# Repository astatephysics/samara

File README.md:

# samara
Red Wolf Space Program's samara-style glider payload

----------------------------------------------------------
## Overview

Samara are a fruit with a fibrous wing-like structure that increases their wind-borne dispersal distances. Some of these like maple and ash seeds may slow their descent by autorotation as such they provide much entertainment for us humans who find them about. This project seeks to develop an airborne payload that mimic this behavior with a 3d printed airframe housing a radio antenna and this printed circuit board. 

This version of the board is contstrained to a 30.5mm x 30.5mm board and is inspired by "CricketSATs." This consists of a RP2040 microcontroller, BME280 temperature/humidity/pressure sensor, BNO055 inertial measurement unit, and RF95 LoRA radio. Several indicator leds are included as well as a surface mounted piezo buzzer. A STEMMA/Qwiic-compatable JST connector provides access to peripheral boards over I2C (e.g., GPS breakout board, realtime clocks, science payloads.)

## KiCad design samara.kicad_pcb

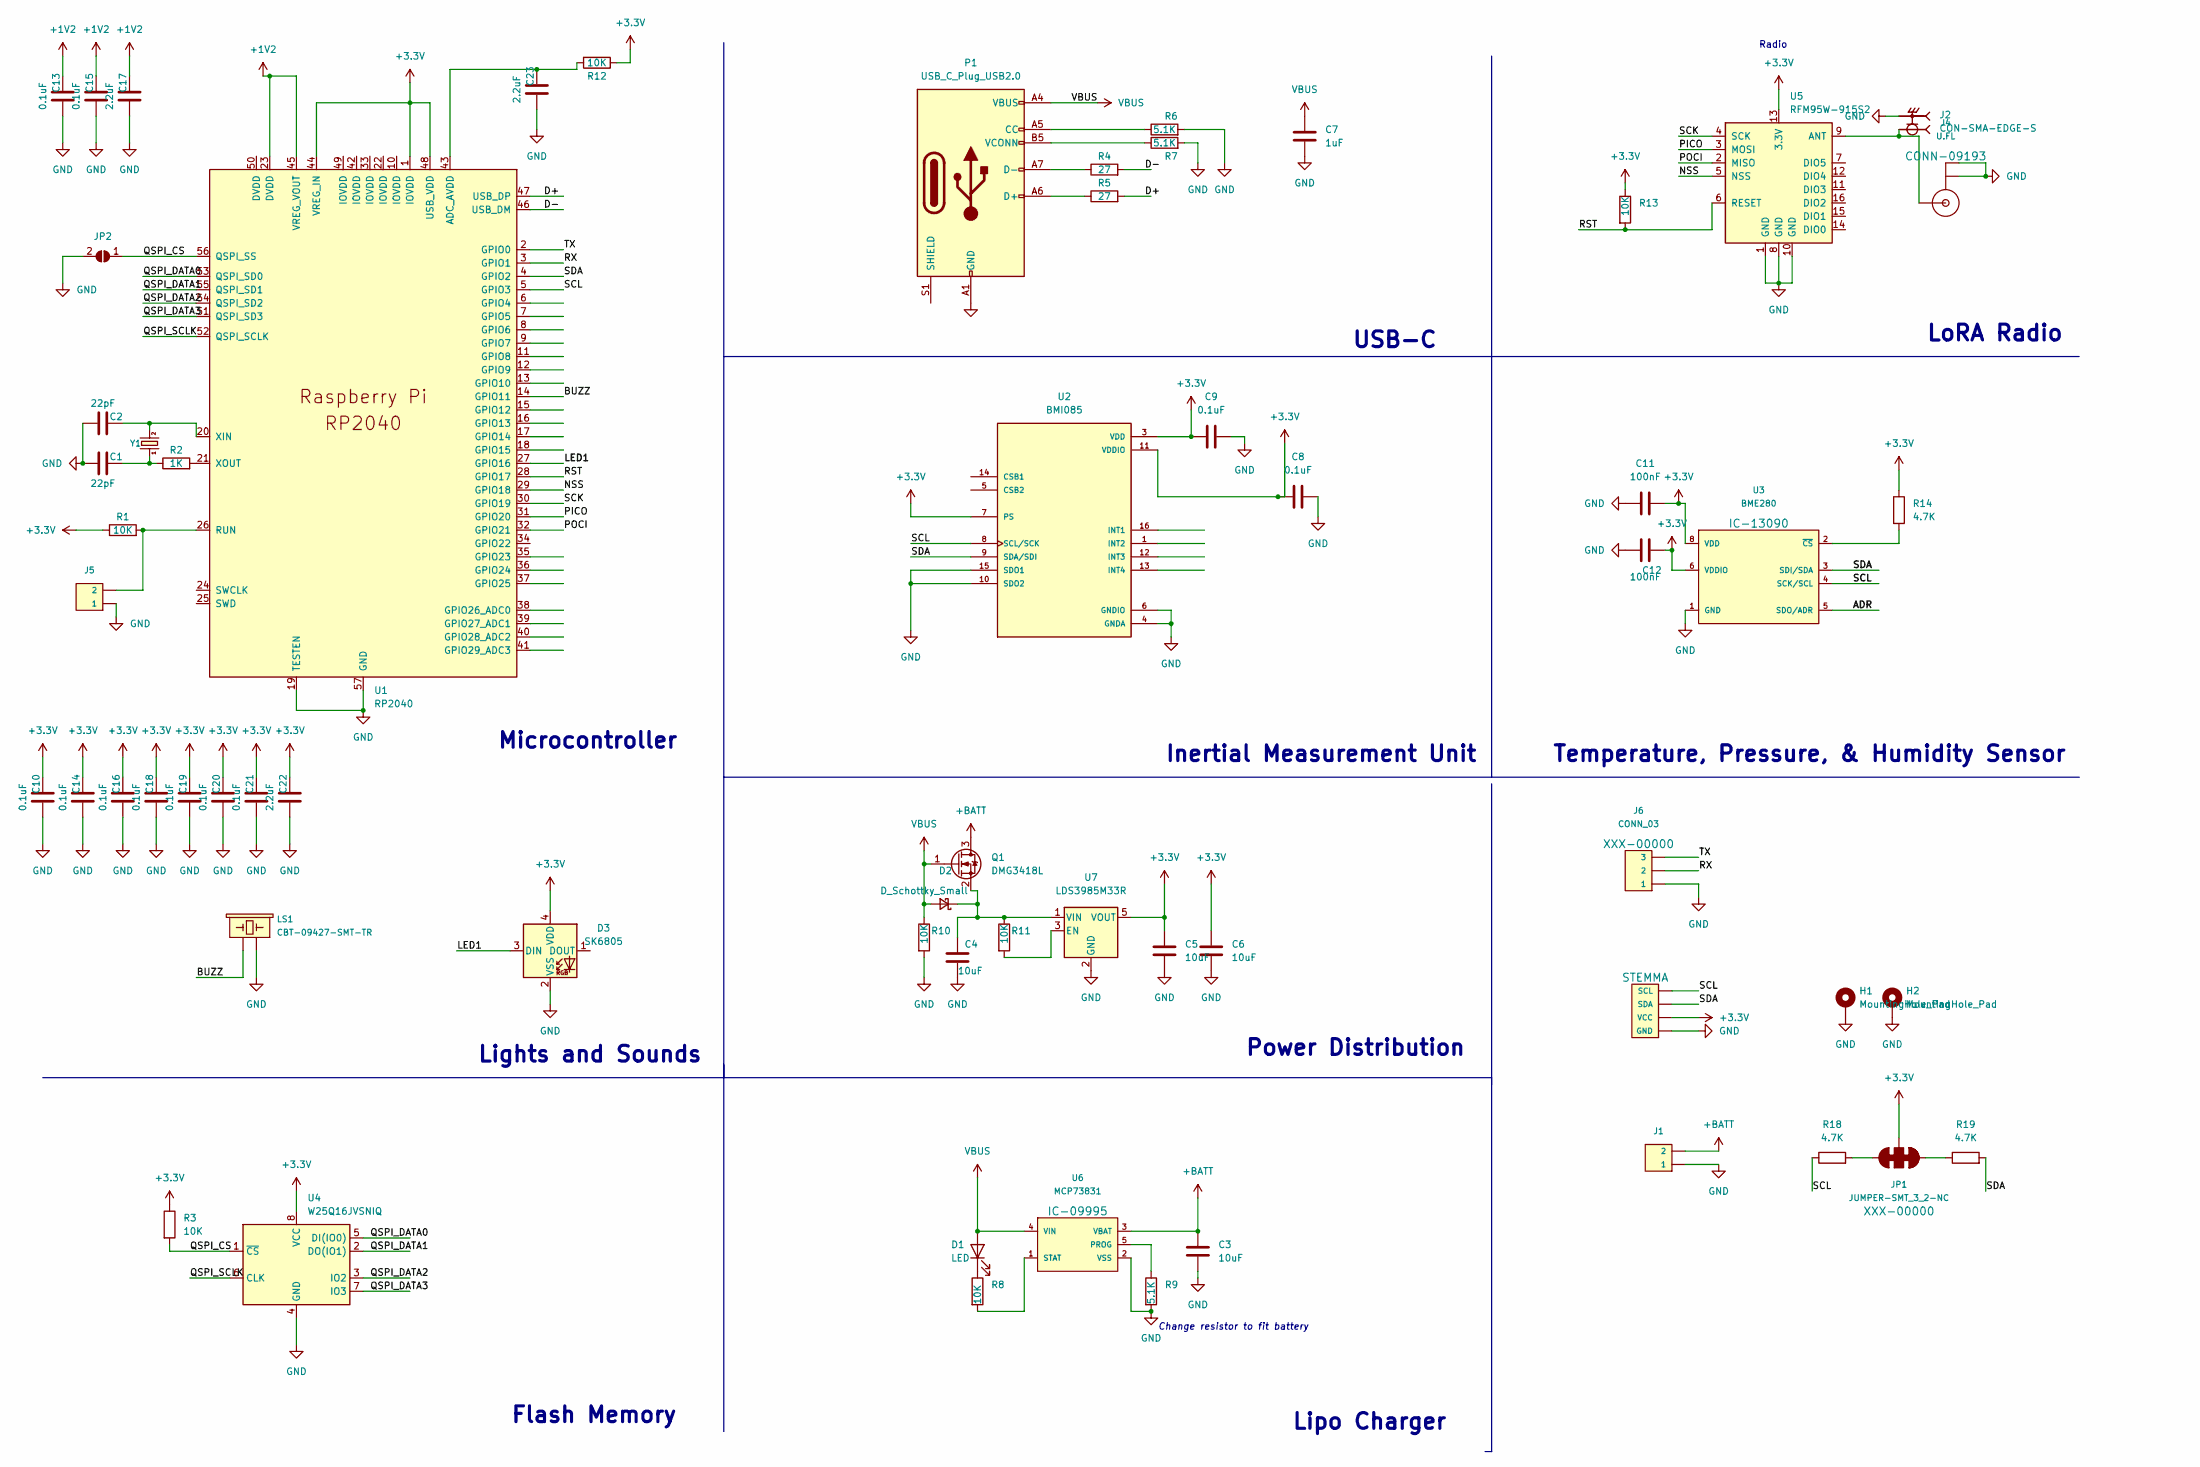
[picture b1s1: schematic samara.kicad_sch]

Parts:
C1, C2: 22pF; C_0402_1005Metric
C3, C4, C5, C6: 10uF; C_0402_1005Metric
C7: 1uF; C_0402_1005Metric
C8, C9, C10, C13, C14, C15, C16, C18, C19, C20, C21: 0.1uF; C_0402_1005Metric
C11, C12: 100nF; C_0402_1005Metric
C17, C22, C23: 2.2uF; C_0402_1005Metric
D1: LED; LED_0603_1608Metric
D2: D_Schottky_Small; D_SOD-128
D3: SK6805; LED_SK6805_PLCC4_2.4x2.7mm_P1.3mm
H1, H2: MountingHole_Pad; MountingHole_2.2mm_M2_DIN965_Pad_TopBottom
J1: CONN_02JST-PTH-2; JST_PH_S2B-PH-SM4-TB_1x02-1MP_P2.00mm_Horizontal
J2: CON-SMA-EDGE-S; RFSOLUTIONS_CON-SMA-EDGE-S; PARTREV 1
J3: I2C_STANDARDQWIIC; 1X04_1MM_RA
J4: U.FL
J5: CONN_02; 1X02
J6: CONN_03; 1X03
JP1: JUMPER-SMT_3_2-NC; SMT-JUMPER_3_2-NC_TRACE_SILK
JP2: SolderJumper_2_Open; SMT-JUMPER_2_NO_NO-SILK
LS1: CBT-09427-SMT-TR; BUZZER-CCV-KIT
P1: USB_C_Plug_USB2.0; USB_C_Receptacle_XKB_U262-16XN-4BVC11
Q1: DMG3418L; SOT-23
R1, R3, R8, R10, R11, R12, R13: 10K; R_0402_1005Metric
R2: 1K; R_0402_1005Metric
R4, R5: 27; R_0402_1005Metric
R6, R7, R9: 5.1K; R_0402_1005Metric
R14, R18, R19: 4.7K; R_0402_1005Metric
U1: RP2040; RP2040-QFN-56
U2: BMI085; PQFN50P450X300X100-16N; PARTREV 1.4
U3: BME280; LGA-8-2.5X2.5
U4: W25Q16JVSNIQ; SOIC-8_3.9x4.9mm_P1.27mm
U5: RFM95W-915S2; HOPERF_RFM9XW_SMD
U6: MCP73831; SOT-23-5
U7: LDS3985M33R; SOT-23-5
Y1: CRYSTAL-12MHZ"; CRYSTAL-SMD-3.2X2.5MM

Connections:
+1V2: C13.2, C15.2, C17.2, U1.23 (DVDD), U1.45 (VREG_VOUT)
+3V3: C5.1, C6.1, C8.1, C9.1, C10.2, C11.2, C12.2, C14.2, C16.2, C18.2, C19.2, C20.2, C21.2, C22.2, D3.4 (VDD), J3.2 (VCC), JP1.2, R1.1, R3.1, R12.1, R13.1, R14.1, U1.1 (IOVDD), U1.44 (VREG_IN), U1.48 (USB_VDD), U2.3 (VDD), U2.7 (PS), U2.11 (VDDIO), U3.6 (VDDIO), U3.8 (VDD), U4.8 (VCC), U5.13 (3.3V), U7.5 (VOUT)
+BATT: C3.1, J1.2, Q1.3 (D), U6.3 (VBAT)
/ADR: U3.5 (SDO/ADR)
/BUZZ: LS1.+ (1), U1.14 (GPIO11)
/D+: R5.2, U1.47 (USB_DP)
/D-: R4.2, U1.46 (USB_DM)
/LED1: D3.3 (DIN), U1.27 (GPIO16)
/NSS: U1.29 (GPIO18), U5.5 (NSS)
/PICO: U1.31 (GPIO20), U5.3 (MOSI)
/POCI: U1.32 (GPIO21), U5.2 (MISO)
/QSPI_CS: JP2.1 (A), R3.2, U1.56 (QSPI_SS), U4.1 (~CS)
/QSPI_DATA0: U1.53 (QSPI_SD0), U4.5 (DI(IO0))
/QSPI_DATA1: U1.55 (QSPI_SD1), U4.2 (DO(IO1))
/QSPI_DATA2: U1.54 (QSPI_SD2), U4.3 (IO2)
/QSPI_DATA3: U1.51 (QSPI_SD3), U4.7 (IO3)
/QSPI_SCLK: U1.52 (QSPI_SCLK), U4.6 (CLK)
/RST: R13.2, U1.28 (GPIO17), U5.6 (RESET)
/RX: J6.2, U1.3 (GPIO1)
/SCK: U1.30 (GPIO19), U5.4 (SCK)
/SCL: J3.4 (SCL), R18.1, U1.5 (GPIO3), U2.8 (SCL/SCK), U3.4 (SCK/SCL)
/SDA: J3.3 (SDA), R19.2, U1.4 (GPIO2), U2.9 (SDA/SDI), U3.3 (SDI/SDA)
/TX: J6.3, U1.2 (GPIO0)
GND: C1.1, C2.1, C3.2, C4.2, C5.2, C6.2, C7.2, C8.2, C9.2, C10.1, C11.1, C12.1, C13.1, C14.1, C15.1, C16.1, C17.1, C18.1, C19.1, C20.1, C21.1, C22.1, C23.1, D3.2 (VSS), H1.1, H2.1, J1.1, J2.G1, J2.G2, J2.G3, J2.G4, J3.1 (GND), J4.1 (GND), J4.2 (GND), J5.1, J6.1, JP2.2 (B), LS1.- (2), P1.A1 (GND), P1.A12 (GND), P1.B1 (GND), P1.B12 (GND), R6.2, R7.2, R9.2, R10.2, U1.19 (TESTEN), U1.57 (GND), U2.4 (GNDA), U2.6 (GNDIO), U2.10 (SDO2), U2.15 (SDO1), U3.1 (GND), U3.7 (GND), U4.4 (GND), U5.1 (GND), U5.8 (GND), U5.10 (GND), U6.2 (VSS), U7.2 (GND)
unnamed: C1.2, R2.1, Y1.1
unnamed: C2.2, U1.20 (XIN), Y1.3 (2)
unnamed: C4.1, D2.1 (K), Q1.2 (S), R11.1, U7.1 (VIN)
unnamed: D1.1 (K), R8.1
unnamed: J2.1, J4.FEED (SIGNAL), U5.9 (ANT)
unnamed: J5.2, R1.2, U1.26 (RUN)
unnamed: JP1.1, R19.1
unnamed: JP1.3, R18.2
unnamed: P1.A5 (CC), R6.1
unnamed: P1.A6 (D+), R5.1
unnamed: P1.A7 (D-), R4.1
unnamed: P1.B5 (VCONN), R7.1
unnamed: R2.2, U1.21 (XOUT)
unnamed: R8.2, U6.1 (STAT)
unnamed: R9.1, U6.5 (PROG)
unnamed: R11.2, U7.3 (EN)
unnamed: R14.2, U3.2 (~CS)
unnamed: C23.2, R12.2, U1.43 (ADC_AVDD)
VBUS: C7.1, D1.2 (A), D2.2 (A), P1.A4 (VBUS), P1.A9 (VBUS), P1.B4 (VBUS), P1.B9 (VBUS), Q1.1 (G), R10.1, U6.4 (VIN)

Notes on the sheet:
Radio
Microcontroller
Flash Memory
Power Distribution
Inertial Measurement Unit
Lipo Charger
LoRA Radio
Lights and Sounds
USB-C
Temperature, Pressure, & Humidity Sensor
Change resistor to fit battery

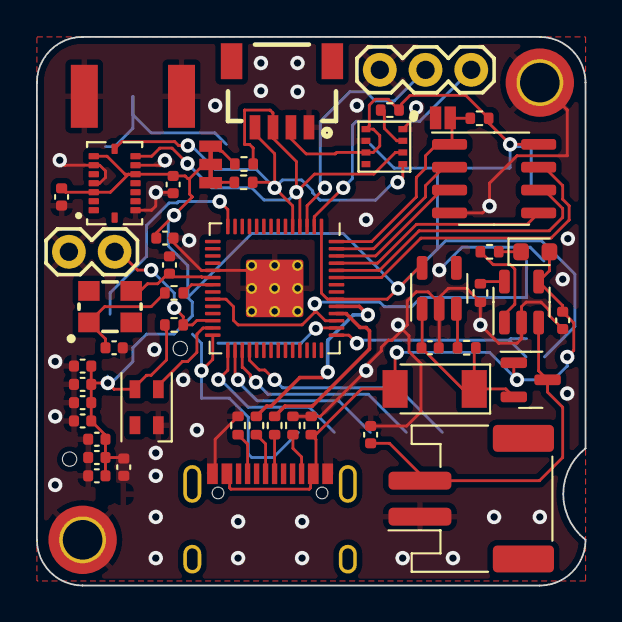
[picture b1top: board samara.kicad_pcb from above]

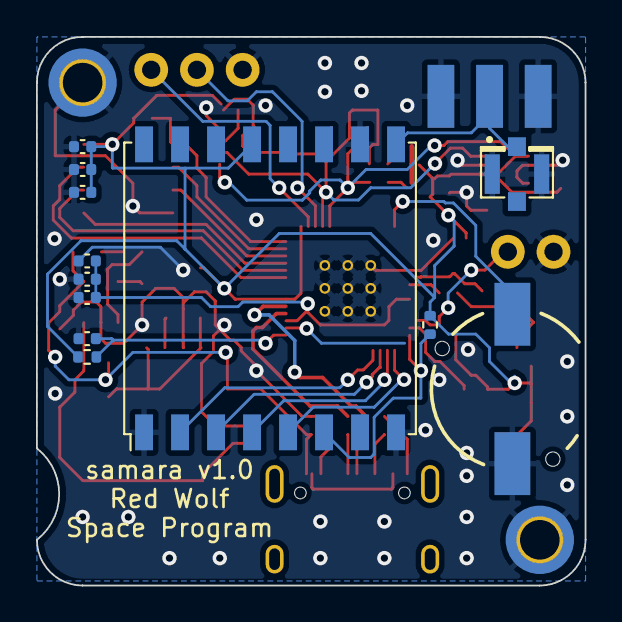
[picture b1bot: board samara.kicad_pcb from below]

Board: 2 copper layers, 30.5 x 30.5 mm, 63 parts (13 on the bottom side), 42 nets.

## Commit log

2022-02-18 initial pcb layout
2022-02-22 updated IMU to BMI085
2022-02-23 update 3d models
2022-03-03 assorted updates and 3d models
2022-03-07 close to v1 production
2022-03-09 ready for first pcb fab
    get ready for bodges...
